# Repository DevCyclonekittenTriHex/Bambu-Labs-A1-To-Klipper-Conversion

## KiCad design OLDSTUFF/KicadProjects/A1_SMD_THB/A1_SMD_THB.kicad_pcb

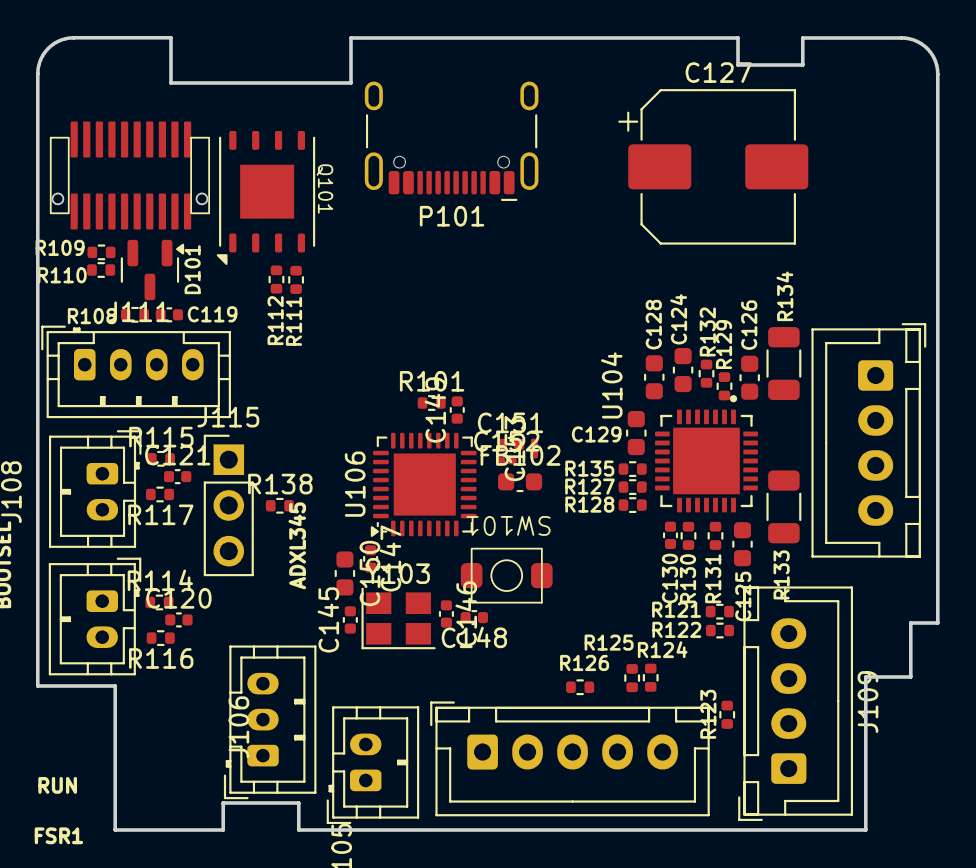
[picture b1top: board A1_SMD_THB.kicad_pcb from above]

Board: 2 copper layers, 50.0 x 44.0 mm, 63 parts (0 on the bottom side), 61 nets, no tracks yet.

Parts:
C119, C120, C121, C130, C147, C148, C149: 100nF; C_0402_1005Metric
C124: 22nF 50V; C_0603_1608Metric
C125, C126, C128: 100nF 50V; C_0603_1608Metric
C127: 100uF; CP_Elec_8x10
C129: 4.7uF; C_0603_1608Metric
C145, C146: 30pF; C_0402_1005Metric
C150: 10uF; C_0603_1608Metric
C151: 10nF; C_0402_1005Metric
C152, C153: 1uF; C_0201_0603Metric
D101: BAV99; SOT-23
EXM101: Conn_01x04; JST_XH_B4B-XH-A_1x04_P2.50mm_Vertical
FB102: 120r 100MHz; C_0603_1608Metric
J104: SGDBM-08-020P-H40; Mezzanine Connector
J105: BL_PROBE; JST_PH_B2B-PH-K_1x02_P2.00mm_Vertical
J106: BL_SERVO; JST_PH_B3B-PH-K_1x03_P2.00mm_Vertical
J107: F_SR2; JST_PH_B2B-PH-K_1x02_P2.00mm_Vertical
J108: F_SR1; JST_PH_B2B-PH-K_1x02_P2.00mm_Vertical
J109: PCF_FAN; JST_XH_B4B-XH-A_1x04_P2.50mm_Vertical
J110: EXF; JST_XH_B5B-XH-A_1x05_P2.50mm_Vertical
J111: ADXL345; JST_PH_B4B-PH-K_1x04_P2.00mm_Vertical
J115: BOOT; PinHeader_1x03_P2.54mm_Vertical
P101: USB_C_Plug; USB_C_Receptacle_HCTL_HC-TYPE-C-16P-01A
Q101: NMOS; PPAK-8L 5x6 Mosfet
R101: 1k; R_0402_1005Metric
R108, R109: 2.37kR; R_0402_1005Metric
R110: 4.7kR; R_0402_1005Metric
R111: 10R; R_0402_1005Metric
R112: 20kR; R_0402_1005Metric
R114, R115: 100; R_0402_1005Metric
R116, R117: 20k; R_0402_1005Metric
R121, R122, R124, R125: 10k; R_0402_1005Metric
R123, R126: 4.7k; R_0402_1005Metric
R127, R128, R129: 20kΩ; R_0402_1005Metric
R130, R131, R132, R135: 100o; R_0402_1005Metric
R133, R134: 100mΩ; R_1206_3216Metric
R138: 10kR; R_0402_1005Metric
SW101: SW_SPST; A Stupid Button
U104: TMC2209-LA; TMC2209-LA-FOOTPRINT
U106: STM32G431KBU3; QFN-32-1EP_5x5mm_P0.5mm_EP3.45x3.45mm
Y103: Crystal_GND24; Crystal_SMD_3225-4Pin_3.2x2.5mm

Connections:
3V3: C130.2, U104.15 (VCC_IO)
+3.3VADC: D101.2 (A), R110.1
+3V3: C147.1, C149.1, C150.1, C153.1, FB102.2, J106.2, J111.1, J115.1, R129.1, U106.1 (VDD), U106.17 (VDD)
+3V3A: C151.1, C152.1, FB102.1, U106.15 (VDDA)
+5V: C129.2, U104.8 (5VOUT)
+24V: C125.2, C126.2, C127.1, C128.1, J104.1, J104.2, J104.3, J104.18, J104.19, J104.20, J109.1, J110.2, P101.A4 (VBUS), P101.A9 (VBUS), P101.B4 (VBUS), P101.B9 (VBUS), R122.1, R125.1, U104.22 (VS), U104.28 (VS)
/accelerometer/SCL: J111.4, U106.25 (PA15)
/accelerometer/SDA: J111.3, U106.30 (PB7)
/mainio/BL_PROBE: J105.2, U106.6 (PA1)
/mainio/BL_SERVO: J106.3, U106.5 (PA0)
/mainio/EXF_PWM: J110.4, R126.1, U106.29 (PB6)
/mainio/EXF_TACH: R124.1, U106.8 (PA3)
/mainio/FIL_SNS1: R115.1, U106.9 (PA4)
/mainio/FIL_SNS2: R114.1, U106.18 (PA8)
/mainio/HE_SIG: R111.1, R112.1, U106.27 (PB4)
/mainio/PCF_PWM: J109.3, R123.1, U106.28 (PB5)
/mainio/PCF_TACH: R121.1, U106.7 (PA2)
/mainio/THO: C119.1, R108.2, U106.26 (PB3)
/mcu_stm32_smol/MT_DIAG: R135.2, U106.10 (PA5)
/mcu_stm32_smol/MT_DIR: R131.1, U106.12 (PA7)
/mcu_stm32_smol/MT_EN: R132.1, U106.11 (PA6)
/mcu_stm32_smol/MT_STEP: R130.1, U106.13 (PB0)
/mcu_stm32_smol/MT_UART_RX: R101.1, U106.20 (PA10)
/mcu_stm32_smol/MT_UART_TX: R101.2, R128.2, U104.14 (~PD_UART), U106.19 (PA9)
/mcu_stm32_smol/USB_D+: P101.A6 (D+), U106.22 (PA12)
/mcu_stm32_smol/USB_D-: P101.A7 (D-), U106.21 (PA11)
GND: C119.2, C125.1, C126.1, C127.2, C129.1, C130.1, C145.2, C146.2, C148.2, C151.2, C152.2, C153.2, D101.1 (K), J104.6, J104.7, J104.14, J104.15, J107.1, J108.1, J109.2, J110.3, J111.2, J115.3, P101.A1 (GND), P101.A12 (GND), P101.B1 (GND), P101.B12 (GND), P101.S1 (SHIELD), Q101.3 (S), R112.2, R123.2, R126.2, R127.1, R128.1, R133.2, R134.2, SW101.1 (A), U104.3 (GND), U104.9 (MS1_AD0), U104.10 (MS2_AD1), U104.18 (GND), U104.29 (EXP), Y103.2, Y103.4
GND3: C120.2, C121.2, J105.1, J106.1
unnamed: C120.1, R114.2, R116.1
unnamed: C121.1, R115.2, R117.1
unnamed: C147.2, C149.2, C150.2
unnamed: D101.3 (K), R108.1, R109.2
unnamed: EXM101.1, U104.1 (OB2)
unnamed: EXM101.2, U104.26 (OB1)
unnamed: EXM101.3, U104.24 (OA1)
unnamed: EXM101.4, U104.21 (OA2)
unnamed: J104.8, J104.9, J104.10, J104.11, J104.12, J104.13, Q101.1 (D)
unnamed: J104.4, J104.5, J104.16, J104.17, R109.1, R110.2
unnamed: J107.2, R116.2
unnamed: J108.2, R117.2
unnamed: J109.4, R121.2, R122.2
unnamed: J110.5, R124.2, R125.2
unnamed: J115.2, R138.1
unnamed: P101.A5 (CC), P101.B5 (VCONN)
unnamed: Q101.2 (G), R111.2
unnamed: C148.1, SW101.2 (B), U106.4 (PG10)
unnamed: R133.1, U104.23 (BRA)
unnamed: R134.1, U104.27 (BRB)
unnamed: R127.2, U104.13 (CLK)
unnamed: C124.1, U104.5 (CPI)
unnamed: C124.2, U104.4 (CPO)
unnamed: R135.1, U104.11 (DIAG)
unnamed: R131.2, U104.19 (DIR)
unnamed: R130.2, U104.16 (STEP)
unnamed: C128.2, U104.6 (VCP)
unnamed: R129.2, R132.2, U104.2 (~EN)
unnamed: R138.2, U106.31 (PB8)
unnamed: C145.1, U106.2 (PF0), Y103.1
unnamed: C146.1, U106.3 (PF1), Y103.3
unnamed: U106.16 (VSS), U106.32 (VSS), U106.33 (VSS)
VBUS: P101.A8 (SBU1), P101.B8 (SBU2)
